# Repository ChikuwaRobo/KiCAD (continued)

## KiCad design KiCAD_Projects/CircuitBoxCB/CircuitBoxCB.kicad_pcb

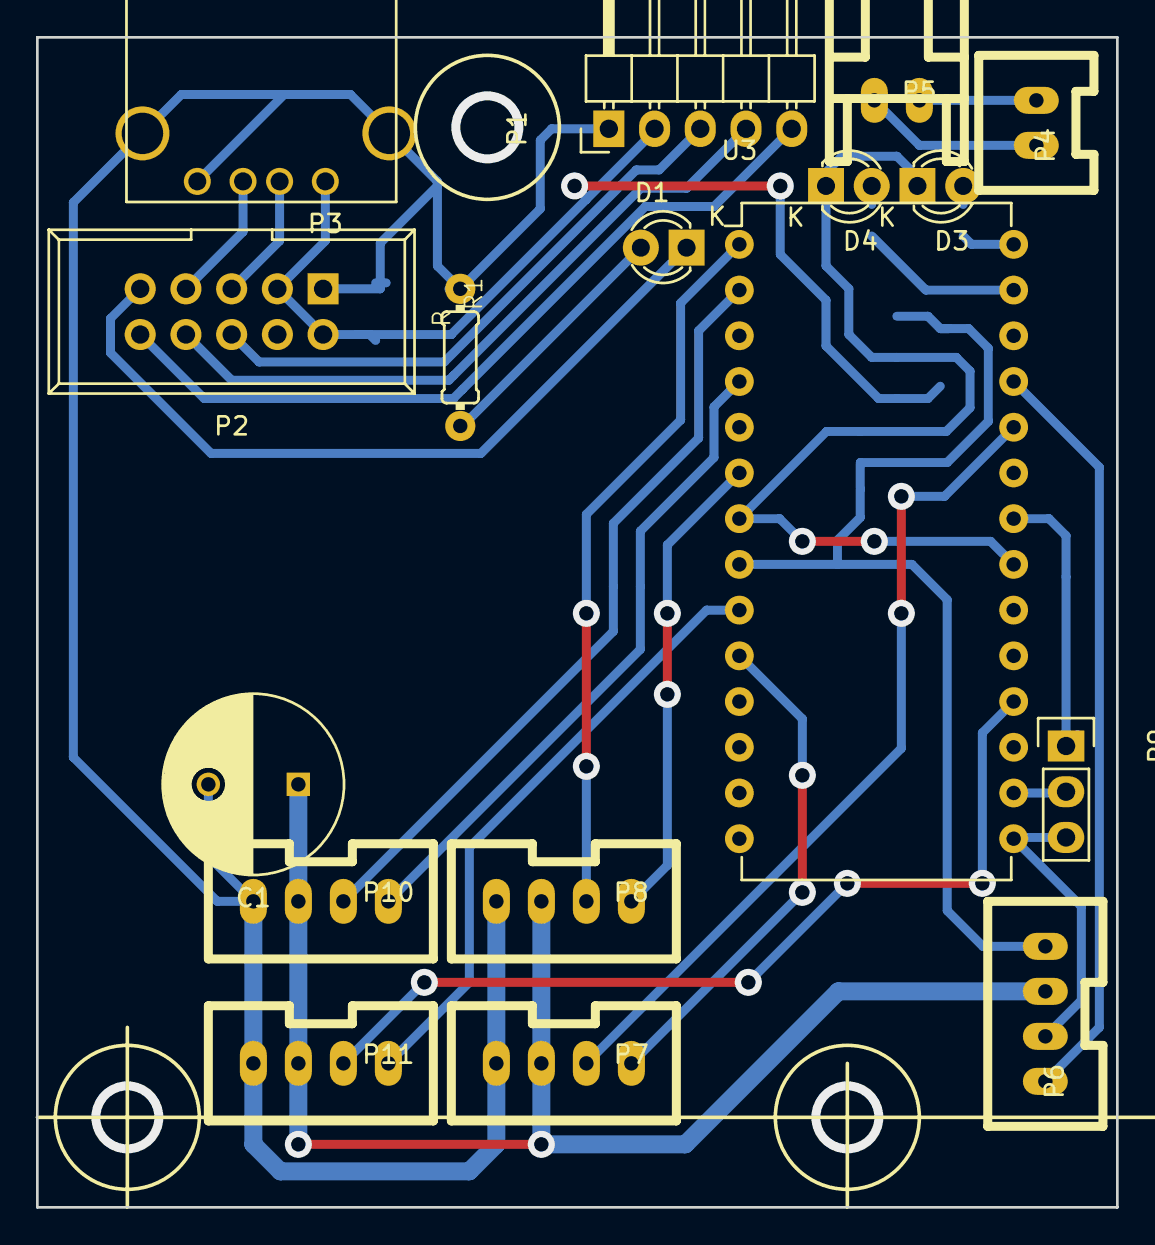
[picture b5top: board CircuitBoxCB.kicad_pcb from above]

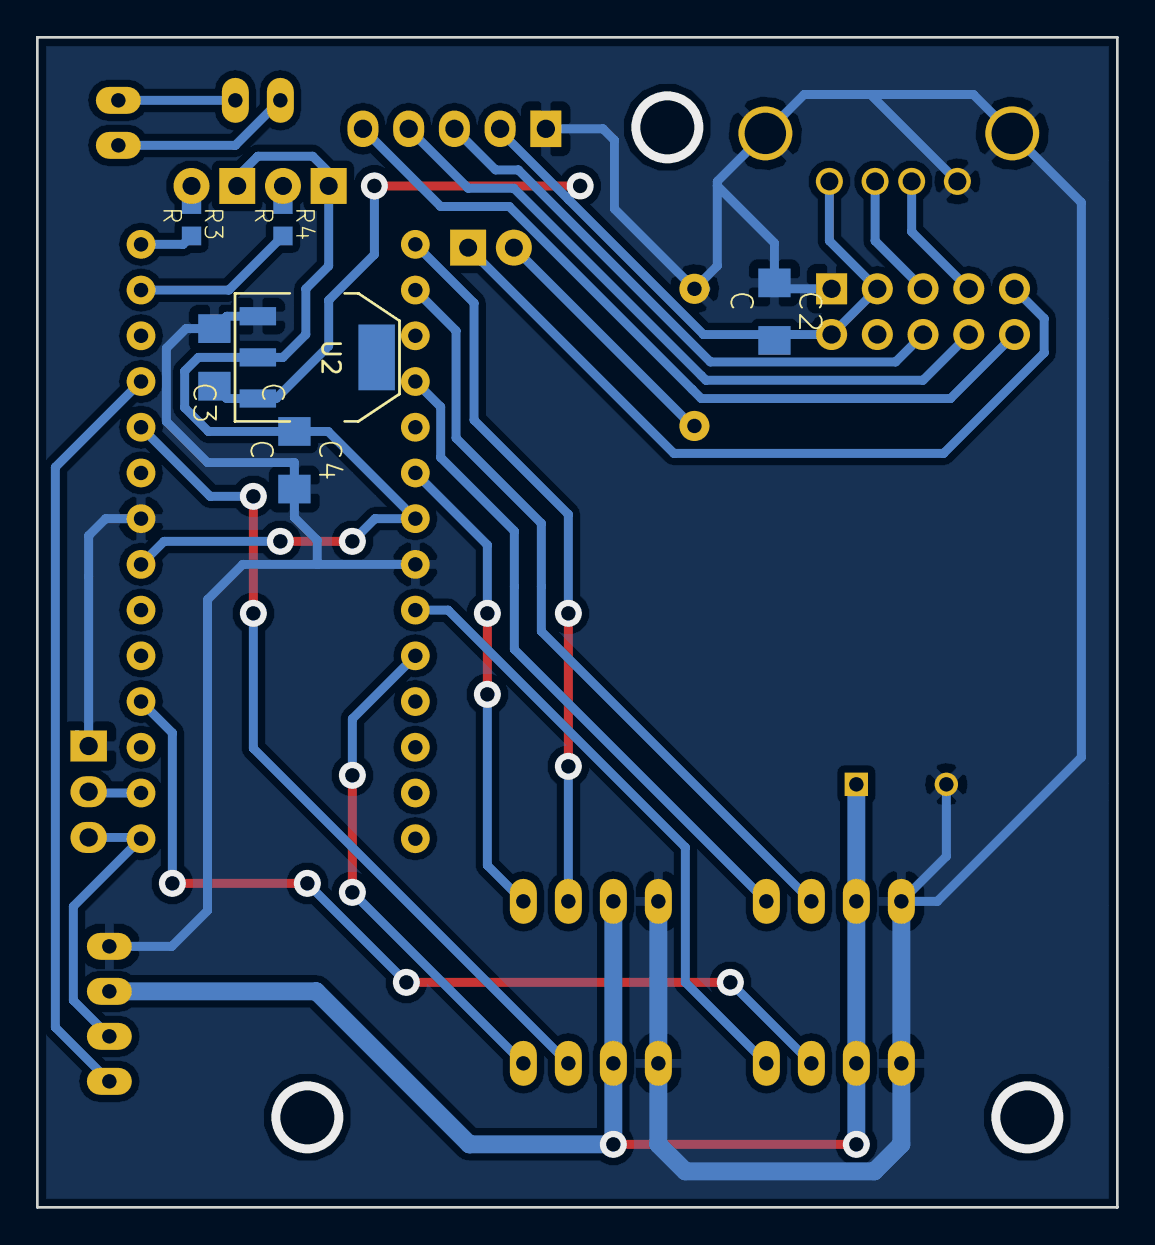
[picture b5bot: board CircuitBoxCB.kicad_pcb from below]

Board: 2 copper layers, 60.0 x 65.0 mm, 23 parts (6 on the bottom side), 28 nets.

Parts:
C1: C; C_Radial_D10_L13_P5
C2, C3, C4: C; C3216
D1, D3, D4: LED; LED-3MM
P1: CONN_01X05; Pin_Header_Angled_1x05
P2: CONN_02X05; IDC_Header_Straight_10pins
P3: USB_A
P4: CONN_01X02; XA_2T
P5: CONN_01X02; XA_2S
P6, P7, P8, P10, P11: CONN_01X04; XA_4T
P9: CONN_01X03; Socket_Strip_Straight_1x03
R1: R; 0204_2f7
R3, R4: R; C0603K
U2: LM1084IT-3.3/NOPB; SOT-223
U3: LPC1114FN28; DIP-28_W15.24mm

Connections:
5V_reray: C1.1, P6.2, P7.2, P8.2, P10.2, P11.2
1114_RX: P6.3, P9.3, U3.15
1114_TX: P9.2, U3.16
+3.3V: C4.1, D3.1, D4.1, U2.2, U3.7, U3.21
+5V: C2.2, C3.1, P1.2, P2.2, P2.3, P3.1, U2.3
EN: P6.4, U3.25
GND: C1.2, C2.1, C3.2, C4.2, P1.1, P2.1, P3.4, P3.5, P6.1, P7.1, P8.1, P9.1, P10.1, P11.1, R1.1, U2.1, U3.8, U3.22
LED_1: R4.2, U3.27
LED_2: R3.2, U3.28
unnamed: D1.1, P2.9
unnamed: D1.2, R1.2
unnamed: D3.2, R3.1
unnamed: D4.2, R4.1
unnamed: P1.3, P2.6
unnamed: P1.4, P2.8
unnamed: P1.5, P2.10
unnamed: P2.5, P3.2
unnamed: P2.7, P3.3
unnamed: P4.1, P5.1
unnamed: P4.2, P5.2
PWM_0: P8.3, U3.1
PWM_1: P10.3, U3.2
PWM_2: P11.3, U3.18
PWM_3: P7.3, U3.24
SIGN_0: P8.4, U3.6
SIGN_1: P10.4, U3.4
SIGN_2: P11.4, U3.9
SIGN_3: P7.4, U3.10

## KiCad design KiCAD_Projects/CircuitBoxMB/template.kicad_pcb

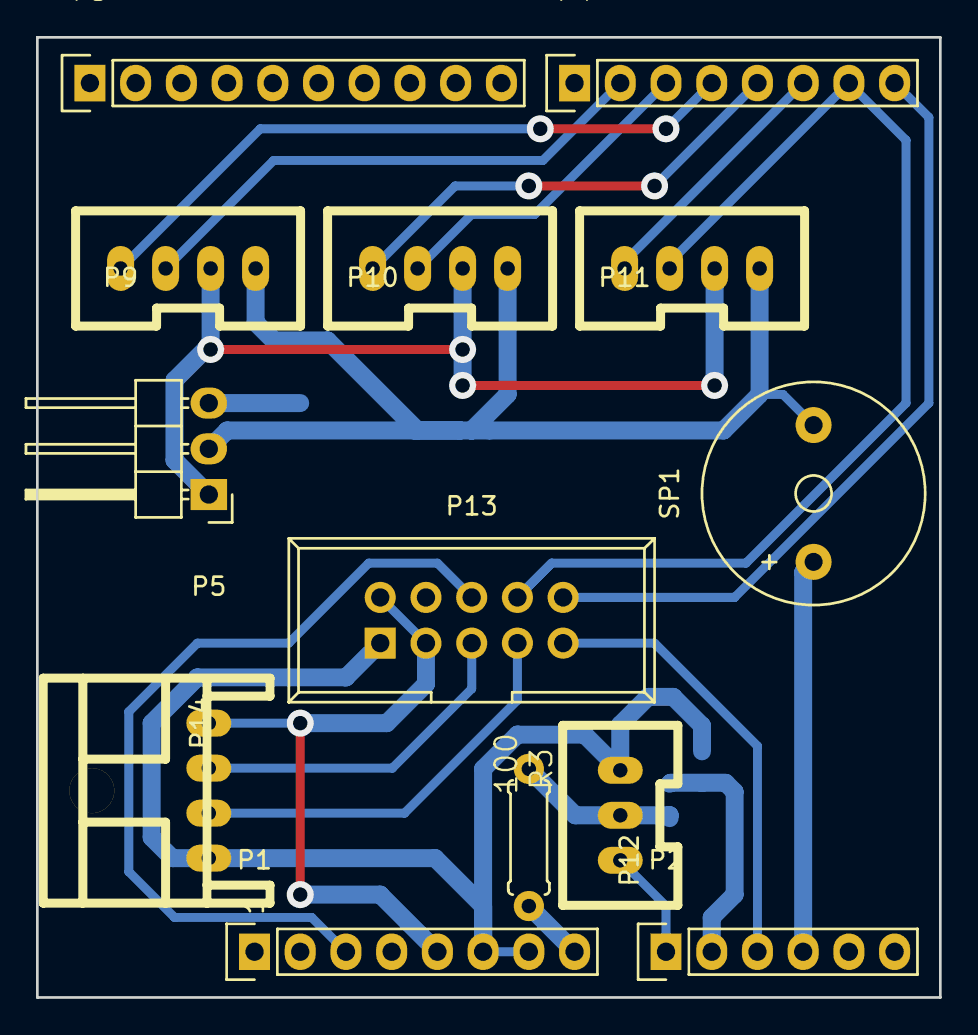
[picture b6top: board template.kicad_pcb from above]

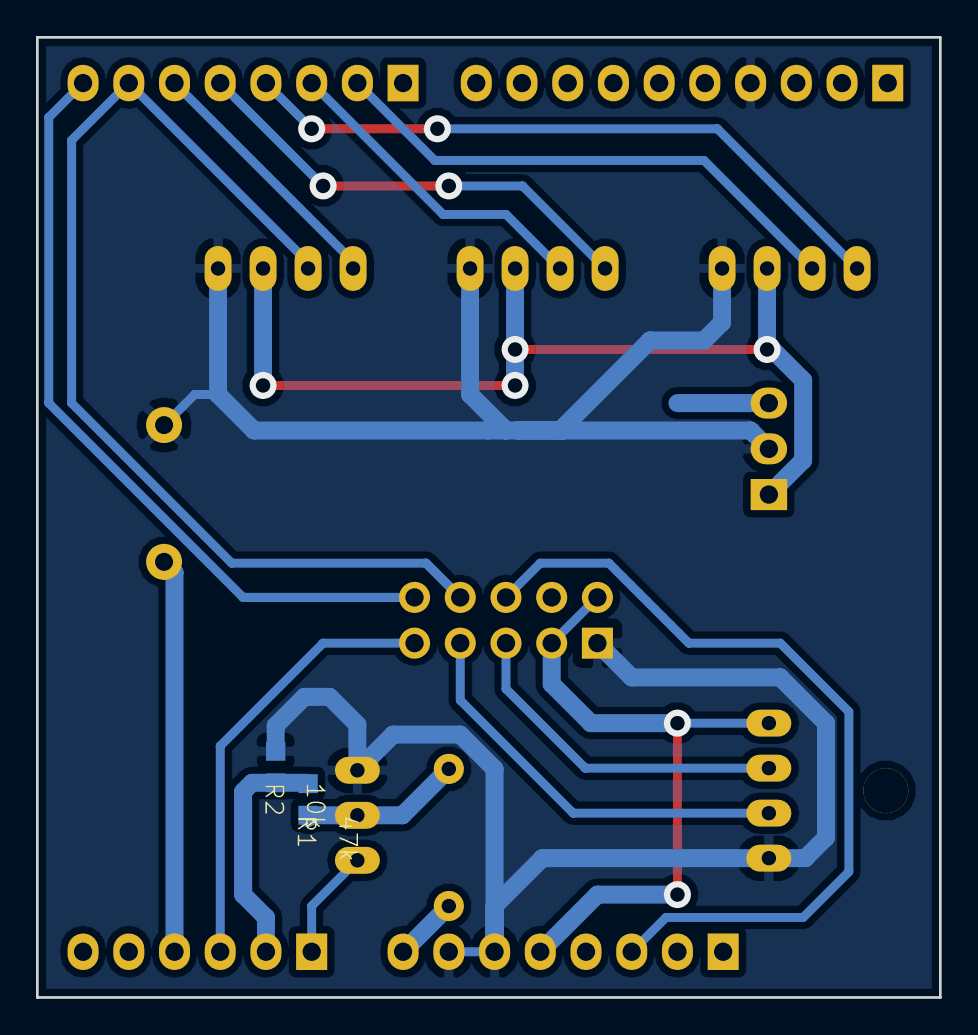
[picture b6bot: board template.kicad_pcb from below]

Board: 2 copper layers, 50.2 x 53.3 mm, 15 parts (2 on the bottom side), 21 nets.

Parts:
P1: Power; Socket_Strip_Straight_1x08
P2: Analog; Socket_Strip_Straight_1x06
P3: Digital; Socket_Strip_Straight_1x10
P4: Digital; Socket_Strip_Straight_1x08
P5: CONN_01X03; Pin_Header_Angled_1x03
P9, P10, P11: CONN_01X04; XA_4T
P12: CONN_01X03; XA_3T
P13: CONN_02X05; IDC_Header_Straight_10pins
P14: CONN_01X04; XA_4S
R1: 47k; C0603K
R2: 10k; C0603K
R3: 100; 0207_2f7
SP1: SPEAKER; Buzzer_12x9.5RM7.6

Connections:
5V_rerays: P5.1, P9.2, P10.2, P11.2
+5V: P1.5, P13.2, P13.3, P14.1
/0(Rx): P4.8, P13.10
/1(Tx): P4.7, P11.3, P13.8
/2: P4.6, P11.4
/3(**): P4.5, P10.4
/4: P4.4, P9.4
/5(**): P4.3, P10.3
/6(**): P4.2, P9.3
/A0: P2.1, P12.3
/A1: P2.2, R1.2, R2.1
/A2: P2.3, P13.9
/A3: P2.4, SP1.1
/A4(SDA): P2.5, P3.2
/A5(SCL): P2.6, P3.1
/Reset: P1.3, P13.6
/Vin: P1.8, P5.3, R3.2
GND: P1.6, P1.7, P3.4, P5.2, P9.1, P10.1, P11.1, P12.1, P13.1, P14.4, R2.2, SP1.2
unnamed: P12.2, R1.1, R3.1
USB_DM: P13.5, P14.2
USB_DP: P13.7, P14.3

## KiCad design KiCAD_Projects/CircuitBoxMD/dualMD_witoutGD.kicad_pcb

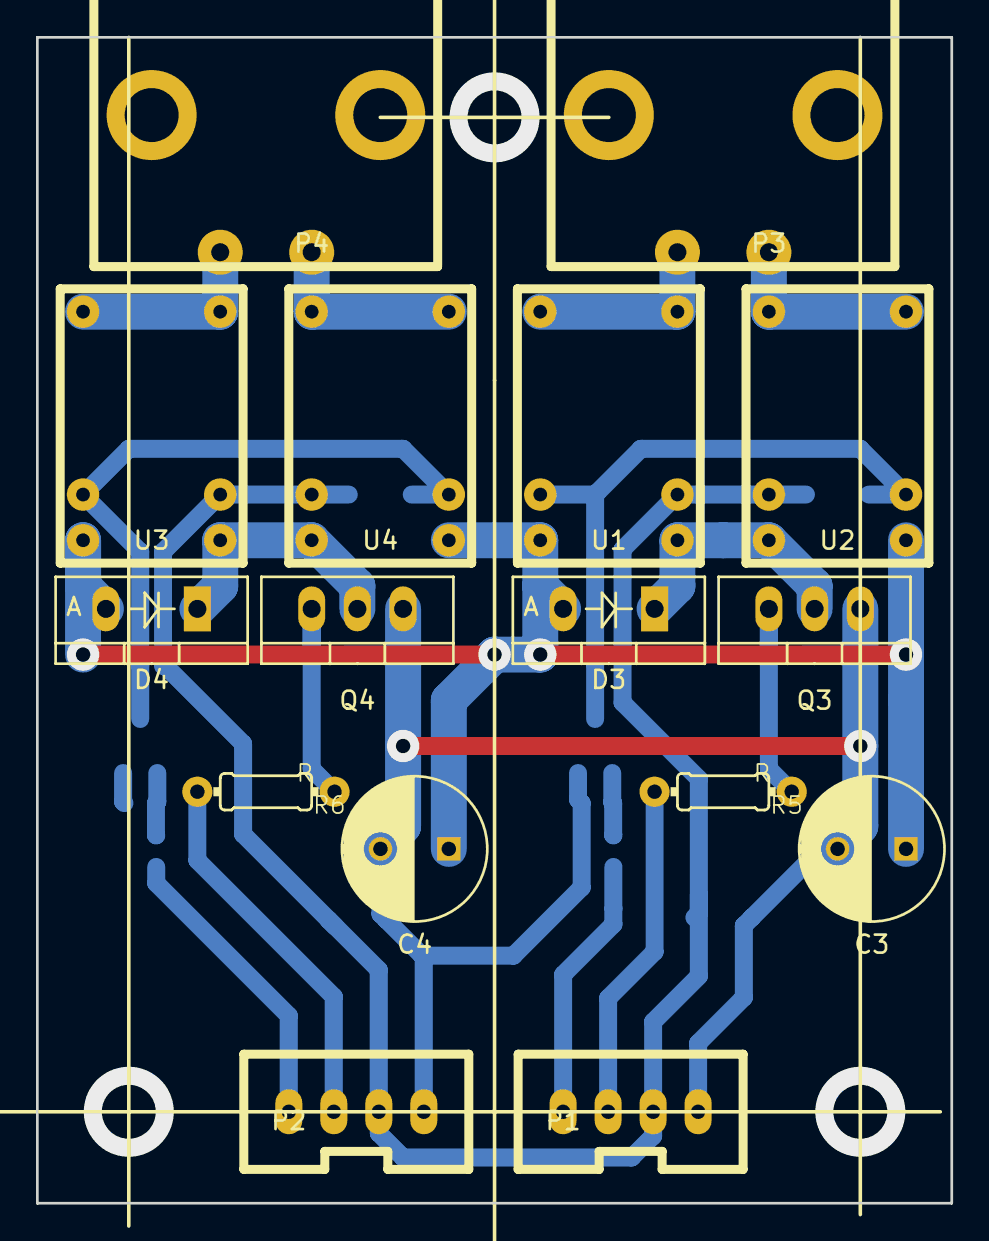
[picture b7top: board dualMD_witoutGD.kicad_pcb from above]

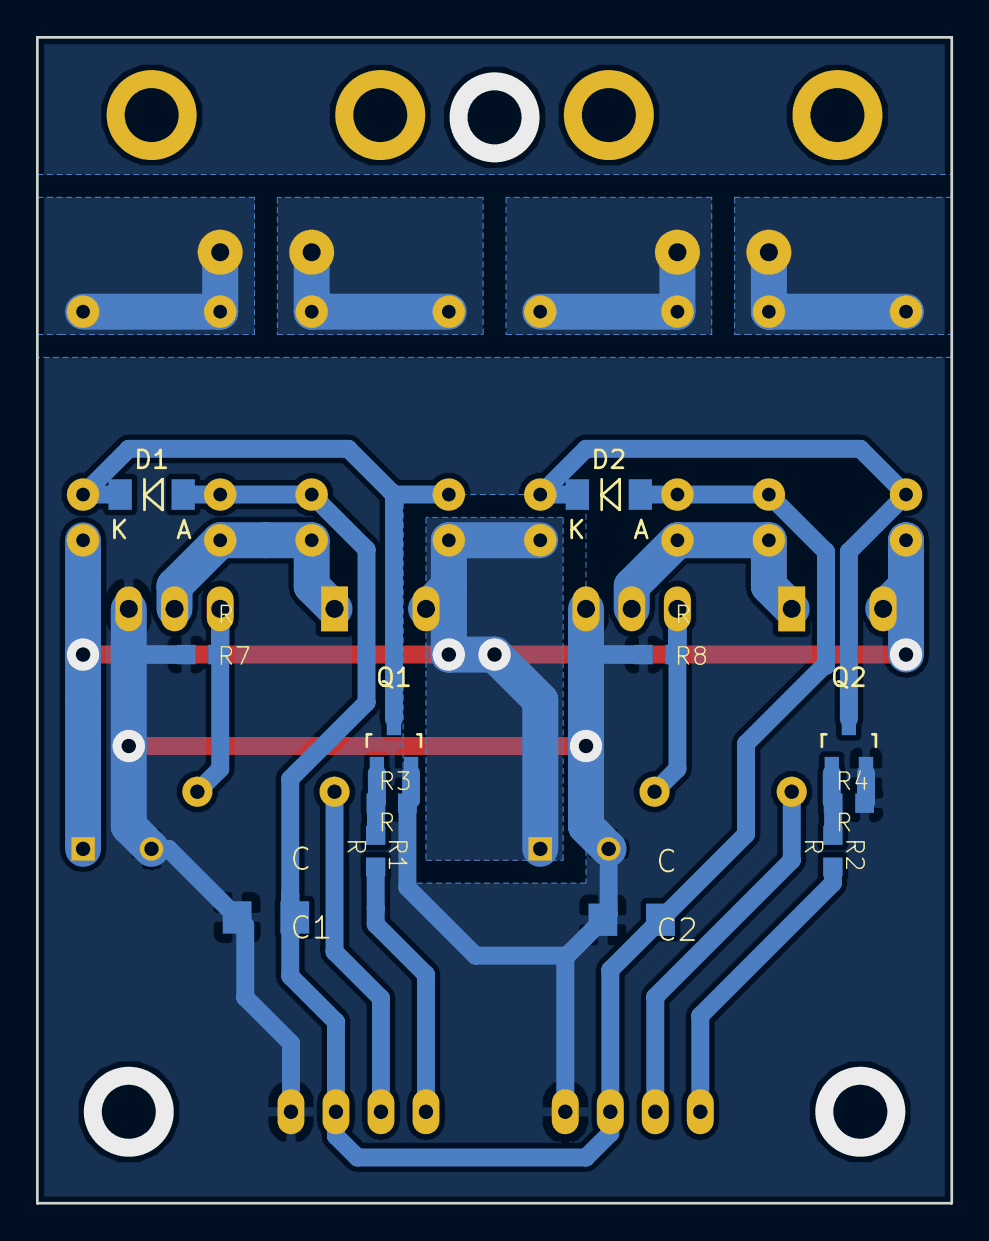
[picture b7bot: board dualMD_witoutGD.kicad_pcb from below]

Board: 2 copper layers, 50.8 x 64.8 mm, 28 parts (12 on the bottom side), 19 nets.

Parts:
C1, C2: C; C3216
C3, C4: C; C_Radial_D8_L21_P3.8
D1, D2: DIODE; MiniMELF_Standard
D3, D4: DIODE; Diode_TO-220_Vertical
P1, P2: CONN_4; XA_4T
P3, P4: CONN_2; D-3200S_2
Q1, Q2: MOS_N; SOT-23_Handsoldering
Q3, Q4: MOS_N; TO-220_Neutral123_Vertical
R1, R2, R3, R4, R7, R8: R; C0603K
R5, R6: R; 0204_2f7
U1, U2, U3, U4: HSIN_946

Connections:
+5V: C1.1, C2.1, D1.2, D2.2, P1.2, P2.2, U1.5, U2.2, U3.5, U4.2
+BATT: C3.1, C4.1, D3.2, D4.2, U1.3, U2.4, U3.3, U4.4
COIL0: D1.1, Q1.D, U1.2, U2.5
COIL1: D2.1, Q2.D, U3.2, U4.5
GND: C1.2, C2.2, C3.2, C4.2, P1.1, P2.1, Q1.S, Q2.S, Q3.S, Q4.S, R3.2, R4.2, R7.2, R8.2
unnamed: P1.3, R5.2
unnamed: P1.4, R1.2
unnamed: P2.3, R6.2
unnamed: P2.4, R2.2
unnamed: P3.1, U2.1
unnamed: P3.2, U1.1
unnamed: P4.1, U4.1
unnamed: P4.2, U3.1
unnamed: Q1.G, R1.1, R3.1
unnamed: Q2.G, R2.1, R4.1
unnamed: Q3.G, R5.1, R7.1
unnamed: Q4.G, R6.1, R8.1
PWM_GND0: D3.1, Q3.D, U1.4, U2.3
PWM_GND1: D4.1, Q4.D, U3.4, U4.3
